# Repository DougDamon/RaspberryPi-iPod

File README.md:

# piPod - Raspberry Pi iPod Clone

A Python-based music player for Raspberry Pi with YouTube download capabilities and a Qt-based GUI.

## Features

- Music playback with playlist management
- YouTube playlist download and conversion
- Qt-based touchscreen GUI
- Album art display
- SQLite music database
- Theme support

## Requirements

- Python 3.7+
- Raspberry Pi (tested on Pi 3/4)
- Qt5/PySide6 for GUI
- yt-dlp for YouTube downloads
- pygame or vlc for audio playback

## Installation

```bash
# Clone repository
git clone https://github.com/DougDamon/RaspberryPi-iPod.git
cd RaspberryPi-iPod

# Install dependencies
pip install -r requirements.txt

# Configure
cp piPod.cfg.example piPod.cfg
# Edit piPod.cfg with your settings

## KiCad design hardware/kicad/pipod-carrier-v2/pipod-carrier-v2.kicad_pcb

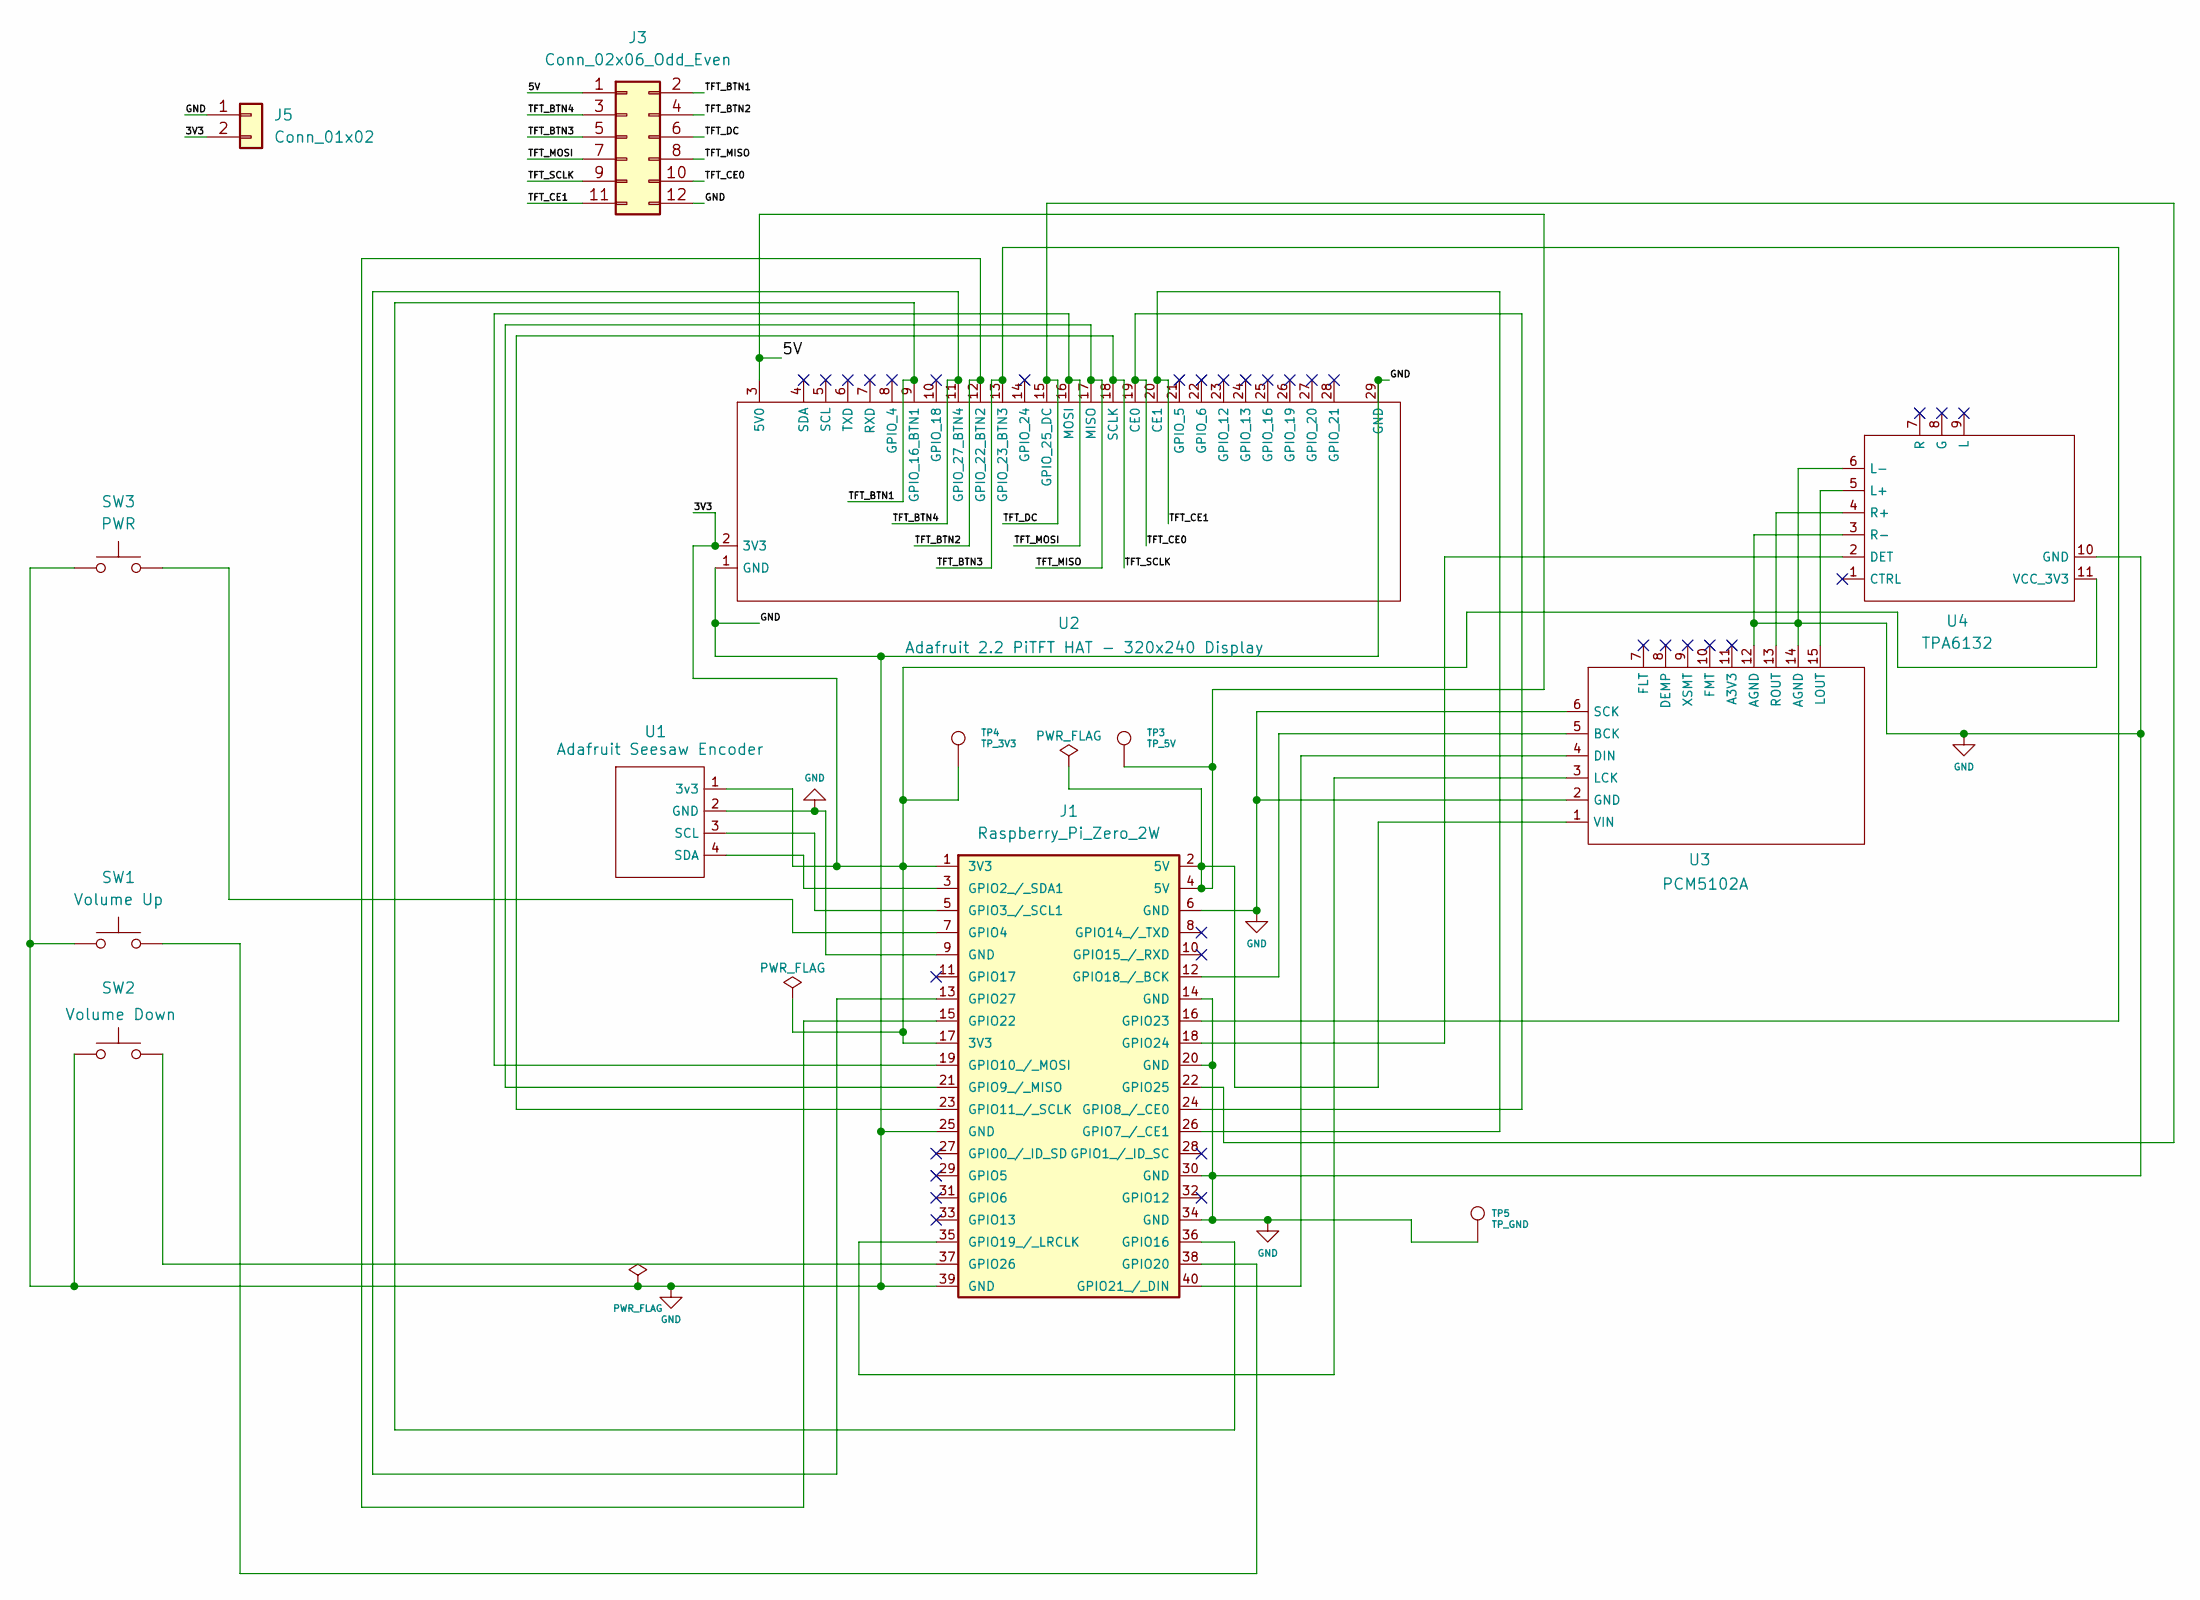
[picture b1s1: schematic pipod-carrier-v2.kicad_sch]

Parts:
J1: Raspberry_Pi_Zero_2W; Raspberry_Pi_Zero_Socketed_THT_FaceDown_MountingHoles
J3: Conn_02x06_Odd_Even; PinHeader_2x06_P2.54mm_Vertical
J5: Conn_01x02; PinHeader_1x02_P2.54mm_Vertical
SW1: Volume Up; SW_Tactile_6x6_RightAngle
SW2: Volume Down; SW_Tactile_6x6_RightAngle
SW3: PWR; SW_Tactile_6x6_RightAngle
TP3: TP_5V; TestPoint_Plated_Hole_D2.0mm
TP4: TP_3V3; TestPoint_Plated_Hole_D2.0mm
TP5: TP_GND; TestPoint_Plated_Hole_D2.0mm
U1: Adafruit Seesaw Encoder; PinHeader_1x04_P2.54mm_Vertical
U2: Adafruit 2.2 PiTFT HAT - 320x240 Display
U3: PCM5102A; GY-PCM5102_PiPod
U4: TPA6132; TPA6132_PiPod

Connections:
/3V3: J1.1 (3V3), J1.17 (3V3), J5.2, TP4.1 (1_1), U1.1 (3v3), U2.2 (3V3), U4.11 (VCC_3V3)
/5V: J1.2 (5V), J1.4 (5V), J3.1, TP3.1 (1_1), U2.3 (5V0), U3.1 (VIN)
/TFT_BTN1: J1.36 (GPIO16), J3.2, U2.9 (GPIO_16_BTN1)
/TFT_BTN2: J1.15 (GPIO22), J3.4, U2.12 (GPIO_22_BTN2)
/TFT_BTN3: J1.16 (GPIO23), J3.5, U2.13 (GPIO_23_BTN3)
/TFT_BTN4: J1.13 (GPIO27), J3.3, U2.11 (GPIO_27_BTN4)
/TFT_CE0: J1.24 (GPIO8_/_CE0), J3.10, U2.19 (CE0)
/TFT_CE1: J1.26 (GPIO7_/_CE1), J3.11, U2.20 (CE1)
/TFT_DC: J1.22 (GPIO25), J3.6, U2.15 (GPIO_25_DC)
/TFT_MISO: J1.21 (GPIO9_/_MISO), J3.8, U2.17 (MISO)
/TFT_MOSI: J1.19 (GPIO10_/_MOSI), J3.7, U2.16 (MOSI)
/TFT_SCLK: J1.23 (GPIO11_/_SCLK), J3.9, U2.18 (SCLK)
GND: J1.6 (GND), J1.9 (GND), J1.14 (GND), J1.20 (GND), J1.25 (GND), J1.30 (GND), J1.34 (GND), J1.39 (GND), J3.12, J5.1, SW1.1, SW2.1, SW3.1, TP5.1 (1_1), U1.2 (GND), U2.1 (GND), U2.29 (GND), U3.2 (GND), U3.6 (SCK), U3.12 (AGND), U3.14 (AGND), U4.3 (R-), U4.6 (L-), U4.10 (GND)
unnamed: J1.3 (GPIO2_/_SDA1), U1.4 (SDA)
unnamed: J1.5 (GPIO3_/_SCL1), U1.3 (SCL)
unnamed: J1.7 (GPIO4), SW3.2
unnamed: J1.12 (GPIO18_/_BCK), U3.5 (BCK)
unnamed: J1.35 (GPIO19_/_LRCLK), U3.3 (LCK)
unnamed: J1.38 (GPIO20), SW1.2
unnamed: J1.40 (GPIO21_/_DIN), U3.4 (DIN)
unnamed: J1.18 (GPIO24), U4.2 (DET)
unnamed: J1.37 (GPIO26), SW2.2
unnamed: U3.15 (LOUT), U4.5 (L+)
unnamed: U3.13 (ROUT), U4.4 (R+)

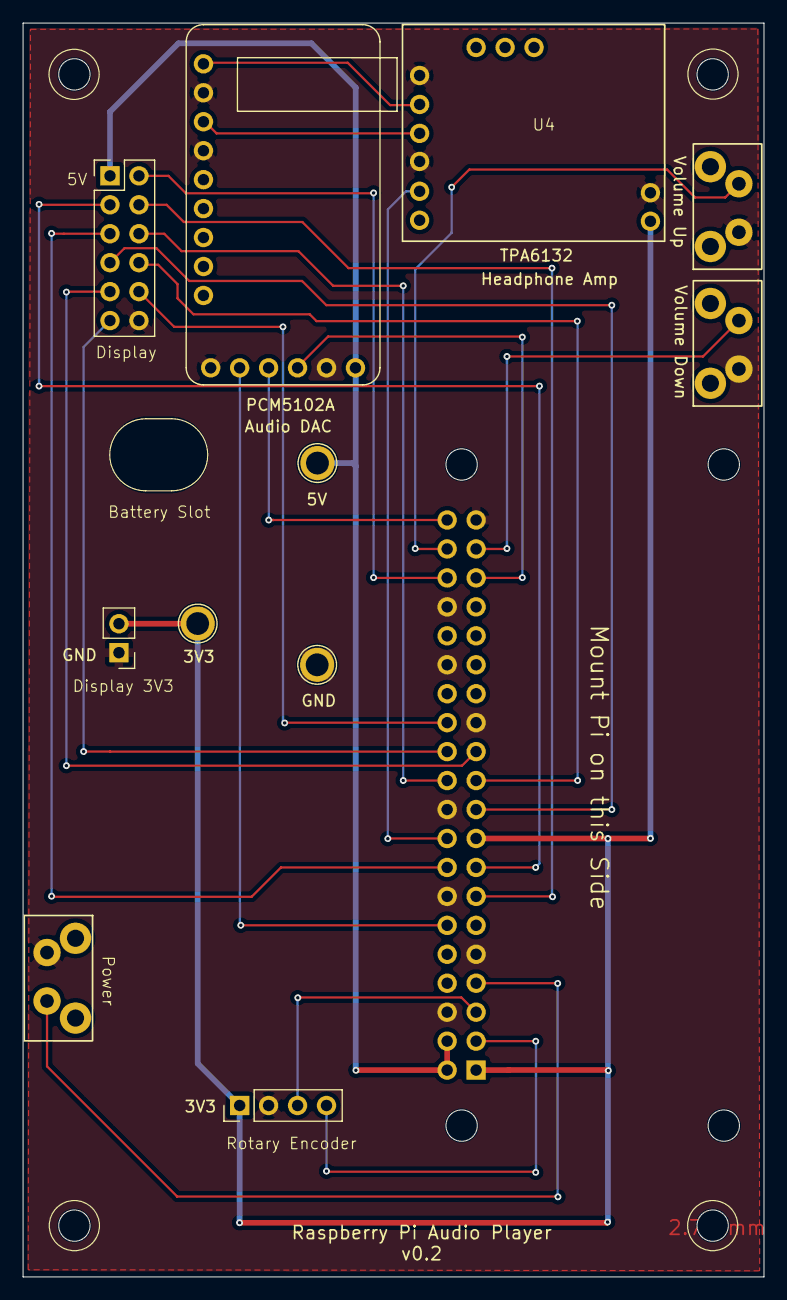
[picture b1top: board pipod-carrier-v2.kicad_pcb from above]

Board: 2 copper layers, 65.0 x 110.0 mm, 13 parts (1 on the bottom side), 24 nets.

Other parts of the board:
Battery Slot: Battery Slot; Battery_Slot

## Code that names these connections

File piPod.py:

from gpiozero import Button
from common.config.settings import ConfigService
import common.pipodgui_navigation as piPodGUI

from common.library.music_database import MusicDB

configuration = ConfigService()

musicDB = MusicDB()

# Side volume buttons.
# Each button connects its GPIO pin to ground when pressed.
volumeUpButton = Button(20, pull_up=True, bounce_time=0.05)
volumeDownButton = Button(26, pull_up=True, bounce_time=0.05)

# PiTFT display buttons.
displayButton1 = Button(16, pull_up=True, bounce_time=0.05)
displayButton2 = Button(22, pull_up=True, bounce_time=0.05)
displayButton3 = Button(23, pull_up=True, bounce_time=0.05)
displayButton4 = Button(27, pull_up=True, bounce_time=0.05)

volumeUpWasPressed = False
volumeDownWasPressed = False

displayButton1WasPressed = False
displayButton2WasPressed = False
displayButton3WasPressed = False
displayButton4WasPressed = False



is_running = True

piPodGUI = piPodGUI.piPodGUINavigation()
clock = piPodGUI.getClock()

# Music
isMusicPlaying = False
isMusicPaused = False
currentPosition = 0

CurrentPlaylistId = None
CurrentTrackId = None
NextTrackSet = False



# UI Navigation
#MainScreenUIElements = {'NowPlaying' : 1 ,  'Music' : 2,  'OTR' : 3, 'Audiobooks' : 4, 'Games' :  5,  'Management' : 6}
while is_running:
    time_delta = clock.tick(60)/1000.0
    encoderActivity = piPodGUI.getEncoderActivity()
    if encoderActivity != None:
        piPodGUI.EncoderNavigation(encoderActivity)

    # Volume Up
    volumeUpIsPressed = volumeUpButton.is_pressed
    
    if volumeUpIsPressed and not volumeUpWasPressed:
        piPodGUI.VolumeUp()
    
    volumeUpWasPressed = volumeUpIsPressed
    
    
    # Volume Down
    volumeDownIsPressed = volumeDownButton.is_pressed
    
    if volumeDownIsPressed and not volumeDownWasPressed:
        print('vol down')
        piPodGUI.VolumeDown()
    
    volumeDownWasPressed = volumeDownIsPressed
    
    
    # PiTFT Button 1 - GPIO16
    displayButton1IsPressed = displayButton1.is_pressed
    
    if displayButton1IsPressed and not displayButton1WasPressed:
        print("Display Button 1 pressed - GPIO16")
    
    displayButton1WasPressed = displayButton1IsPressed
    
    
    # PiTFT Button 2 - GPIO22
    displayButton2IsPressed = displayButton2.is_pressed
    
    if displayButton2IsPressed and not displayButton2WasPressed:
        print("Display Button 2 pressed - GPIO22")
    
    displayButton2WasPressed = displayButton2IsPressed
    
    
    # PiTFT Button 3 - GPIO23
    displayButton3IsPressed = displayButton3.is_pressed
    
    if displayButton3IsPressed and not displayButton3WasPressed:
        print("Display Button 3 pressed - GPIO23")
    
    displayButton3WasPressed = displayButton3IsPressed
    
    
    # PiTFT Button 4 - GPIO27
    displayButton4IsPressed = displayButton4.is_pressed
    
    if displayButton4IsPressed and not displayButton4WasPressed:
        print("Display Button 4 pressed - GPIO27")
    
    displayButton4WasPressed = displayButton4IsPressed    
        
    for event in piPodGUI.getEvent():
        piPodGUI.manager.process_events(event)
#        print(f'Event: {event}')
        match event.type:
            case piPodGUI.QUIT:
                is_running = False
            case piPodGUI.UI_BUTTON_PRESSED:
                match event.ui_element:
                    case piPodGUI.bNowPlaying:
                            piPodGUI.setCurrentScreenElement(
                                "NowPlaying",
                                "Play/Pause"
                            )
                            piPodGUI.MainScreenHide()
                            piPodGUI.NowPlayingScreenShow()
                    case piPodGUI.bMusic:
                        piPodGUI.MainScreenHide()
                        piPodGUI.MusicScreenShow()
                    case piPodGUI.bPlaylists:
                        piPodGUI.MusicScreenHide()
                        piPodGUI.AvailablePlaylistsScreenShow()
                    case piPodGUI.bPlay:
                        piPodGUI.Play()
#                        piPodGUI.Pause()
#                        piPodGUI.display.flip()
#                        piPodAudio.playTrack()
                        isMusicPlaying = True
                        isMusicPaused = False
                    case piPodGUI.bPause:
                        piPodGUI.Pause()
#                        piPodGUI.display.flip()
#                        piPodGUI.piPodAudio.pauseTrack()
                        NextTrack = None
                        isMusicPaused = True                    
                    case piPodGUI.bForward:
                        piPodGUI.NextTrackNowPlaying()
                    case piPodGUI.bRewind:
                        isMusicPlaying = False
                        piPodGUI.PreviousTrackNowPlaying()
                        isMusicPlaying = True
                    case piPodGUI.bHome:
                        print('home')
                        piPodGUI.NowPlayingScreenHide()
                        piPodGUI.MainScreenShow()
                    case _:
                        pass
            case piPodGUI.UI_SELECTION_LIST_NEW_SELECTION:
                match event.ui_element:
                    case piPodGUI.sPlaylistSelectionList:
                        piPodGUI.NowPlayingScreenShow()
                        selectedPlaylist = piPodGUI.sPlaylistSelectionList.get_single_selection()
                        SelectedNowPlayingPlaylistId = musicDB.getPlaylistIdbyNamefromDB(selectedPlaylist)
                        piPodGUI.setCurrentPlaylist(SelectedNowPlayingPlaylistId)
                        piPodGUI.PlaylistTracksScreenShow()                 
                    case piPodGUI.sPlaylistTracks:
                        piPodGUI.PlaylistTracksScreenHide()
                        selectedTrack = piPodGUI.sPlaylistTracks.get_single_selection()
                        SelectedNowPlayingTrackId = str(musicDB.getTrackIdByNameFromDB(SelectedNowPlayingPlaylistId,  selectedTrack))
#                        NowPlayingContainer,  piPodAudioControls = piPod.NowPlayingScreen() #SelectedNowPlayingPlaylistId,  SelectedNowPlayingTrackId)
                        piPodGUI.PlaylistTracksScreenHide()
                        piPodGUI.setCurrentTrack(SelectedNowPlayingTrackId)
                        piPodGUI.NowPlayingScreenShow()
                    case _:
                        pass
#                        print('other')
            case piPodGUI.MUSIC_END:
                piPodGUI.NextTrackNowPlaying()
#                print('MusicEndEvent',  piPodGUI.MUSICENDEVENT)
            case _:
                pass
    if isMusicPlaying == True or piPodGUI.AudioPlaying == True:
        piPodGUI.updateCurrentPosition()
        
#        if not NextTrackSet:
#            print('Setting Next Track')
#            piPodGUI.setNowPlayingNextTrack()
#            print()
            
#    piPodGUI.manager.process_events(event)
    piPodGUI.manager.update(time_delta)
    
    if piPodGUI.CurrentScreen == "NowPlaying":
    
        if piPodGUI.isDirty():
            piPodGUI.drawNowPlayingDirect()
    
        elif piPodGUI.isPositionDirty():
            piPodGUI.drawCurrentPosition()
    
    
    elif piPodGUI.CurrentScreen == "AvailablePlaylists":
    
        if piPodGUI.isDirty():
            piPodGUI.drawAvailablePlaylistsDirect()
    
    
    elif piPodGUI.CurrentScreen == "PlaylistTracks":
    
        if piPodGUI.isDirty():
            piPodGUI.drawPlaylistTracksDirect()
    
    elif piPodGUI.CurrentScreen == "Artists":

        if piPodGUI.isDirty():
            piPodGUI.drawArtistsDirect()
        
    else:
    
        if piPodGUI.isDirty():
            piPodGUI.drawScreen()
            piPodGUI.updateDisplay()
            piPodGUI.clearDirty()
            piPodGUI.clearPositionDirty()
     
volumeUpButton.close()
volumeDownButton.close()

displayButton1.close()
displayButton2.close()
displayButton3.close()
displayButton4.close()

piPodGUI.quit()

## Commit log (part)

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2024-01-03 Initial code check in
2024-04-10 Initial set of icons
2024-04-10 Initial QT screen definitions
2024-06-19 Add files via upload
    Initial check in of ui code. Definitely nothing is working yet
2024-08-10 Changes to YTM downloader
2024-08-12 Changes to YTM downloader code
2024-08-12 moved this file to YT_Playlist_Downloader directory
2024-08-14 Code cleanup
2024-08-18 Adding GUI
2024-08-26 Updated screens, added some themes, imporved functionality
2024-08-31 Class changes and added start of audio playback
2024-09-07 added skip and play complete playlist. Started Rewind
    Additional Code cleanup
2024-09-25 Fixing git mess up
2024-09-28 Finsihed forward/rewind, adding navigation
2024-11-24 Adding Rotary Encoder support
2024-12-07 Adding Rotary Encoder Navigation
2024-12-07 Added more Encoder navigation
2025-01-01 GUI updates
    Working repeat and added un/shuffle code. Some theme work so the GUI
    looks a bit better
2026-06-29 typo fix
2026-06-30 step 1 in refactor
